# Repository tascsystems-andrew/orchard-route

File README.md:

# Orchard Route

**A GPU place-and-route engine for KiCad, native to Apple Silicon.**

Orchard Route routes printed circuit boards on the Mac GPU using
[MLX](https://github.com/ml-explore/mlx) and hand-written Metal kernels — no CUDA,
no cloud, no external EDA tooling in the loop. It reads a `.kicad_pcb`, negotiates
every net's copper simultaneously on the GPU, and writes back a routed board that
KiCad opens directly.

The name is a tip of the hat to
[OrthoRoute](https://github.com/bbenchoff/OrthoRoute), whose functional intent —
Manhattan-lattice GPU routing for KiCad — this project rebuilds natively for
Apple Silicon. No OrthoRoute code was ported; the architecture was redesigned
around what Metal and unified memory are actually good at.

## Status — working prototype

Flagship result (2026-07-18, MacBook Pro M4 Pro): a real 300×279 mm, 487-net
amplifier board — **all 410 routable nets negotiated to a fully legal routing**
(zero copper overlaps), 29.5 m of track, 1,259 vias (down from 2,824 at the
first legal route the same morning), 45°-smoothed output, ~7 minutes end-to-end
including parsing and write-back.

What works today:

- **`board.py`** — pure-Python `.kicad_pcb` parser (KiCad 5/9/10, no `pcbnew` needed)
- **`lattice.py`** — vectorized board → CSR lattice (both-directions layer model
  with direction preference; true rotated pad ownership; intentional pad-overlap
  allowances)
- **`wavefront.py`** — batched min-plus wavefront SSSP as an `mx.fast.metal_kernel`;
  the pull formulation needs **no atomics**, and 128 nets route per kernel launch
  (~0.5 ms per net; routing 32 nets costs the same wall-clock as routing 1)
- **`pathfinder.py`** — parallel PathFinder negotiation with asymmetric rip-up,
  keeper alternation, windowed stall escape, a post-legal refine pass, and
  legality-checked 45° smoothing; output is always legal, never optimistic
- **`constraints.py` / `place.py`** — the closed analog-constraint vocabulary and
  a deterministic annealing placement explorer (the router-independent half of
  `optimize_region`)
- **`backtrace.py` / `render.py` / `writeback.py`** — distance fields → paths →
  SVG render → routed *copies* of the board (tracks, vias, and component moves)
  that `kicad-cli` loads clean

Honest limitations, today: clearance classes are not yet enforced (grid pitch is
the de-facto clearance — active work), routing is 2-layer only (inner layers
unmodeled), a handful of nets on dense boards hit a known multi-party negotiation
standoff (active work), and the region place-and-route loop is designed
([REGION_SOLVER.md](REGION_SOLVER.md)) but not yet wired together.

## Benchmarks — measured against human ground truth

Seven open-hardware boards with professional placement and human routing
(KiCad's demo boards, Raspberry Pi's RP2040 reference designs, SparkFun's
RP2350 RedBoard, 1BitSquared's iCEBreakers). Protocol: keep the placement,
strip the human's tracks and vias, re-route from scratch, compare
(`bench/run_bench.py`; board sources and licenses in `bench/boards/SOURCES.md`).

| board | nets routed | wirelength vs human | vias vs human |
|---|---|---|---|
| SparkFun RedBoard RP2350 | **108/108** | **0.92×** | **0.78×** |
| iCEBreaker bitsy | 65/65 | 0.96× | 1.73× |
| KiCad pic-programmer | 34/34 | 1.03× | 8 vs 6 |
| RPi Pico VGA reference | 61/61 | 1.25× | 1.17× |
| RPi RP2040 minimal | 51/51 | 1.25× | 2.36× |
| iCEBreaker v1.0e | 123/126 | 1.18× | 1.98× |
| KiCad video demo (589 nets) | 369/371 | 1.09× | 2.52× |

Overall: 811/816 nets (99.4%), each board routed in 0.4–8 s of GPU negotiation
on an M4 Pro. On the SparkFun board the router beats the human layout on both
wirelength and via count simultaneously.

Read the ratios honestly: the router used **two** copper layers everywhere; the
humans had four on five of these boards (a handicap *against* the router — the
harness quantifies it per board). In the other direction, human copper passes
real clearance DRC while the router currently approximates clearance with grid
pitch — closing that gap is active work, as are the remaining 5 nets (a known
multi-party negotiation standoff pattern) and the via gap on dense 2-layer
boards (direction-preference calibration).

## Where it's going

The destination is not "another autorouter." It's an **agent-callable
place-and-route tool**:

```
optimize_region(components, region, constraints, k_candidates)
    -> ranked candidates + diagnostics
```

— hand an AI assistant a group of components, a patch of board, and constraints in a
closed vocabulary, and it places *and* routes just that region, returning ranked
options and machine-readable diagnostics ("net X unrouted, blocked by C8's courtyard;
4 mm more room east would clear it"). Full design in [ARCHITECTURE.md](ARCHITECTURE.md).

## Requirements

- Apple Silicon Mac (developed on M4 Pro; scales with GPU cores and unified memory)
- Python 3.12+, `mlx`, `numpy`
- KiCad 9/10 board files (KiCad itself only needed if you want `kicad-cli` DRC)

## Quickstart

```sh
python -m venv .venv && .venv/bin/pip install mlx numpy
.venv/bin/python pathfinder.py your_board.kicad_pcb --pitch 0.5 --layers F.Cu,B.Cu --svg out/routed.svg
.venv/bin/python writeback.py your_board.kicad_pcb out/routed.kicad_pcb --pitch 0.5 --layers F.Cu,B.Cu
```

Your input board is never modified; write-back refuses to write into the source
board's directory.

## License

Orchard Route is **dual-licensed**:

- **AGPL-3.0-only** (see [LICENSE](LICENSE)) for open use: if you distribute it,
  or run a modified version for others over a network, you must share your source.
- **Commercial licenses** for any use the AGPL doesn't fit — see
  [COMMERCIAL-LICENSE.md](COMMERCIAL-LICENSE.md).

Contributions require a lightweight relicensing grant — see
[CONTRIBUTING.md](CONTRIBUTING.md) before opening a PR.

Copyright © 2026 Andrew Sanche.

<!-- I got a fever, and the only prescription is more cowbell. -->

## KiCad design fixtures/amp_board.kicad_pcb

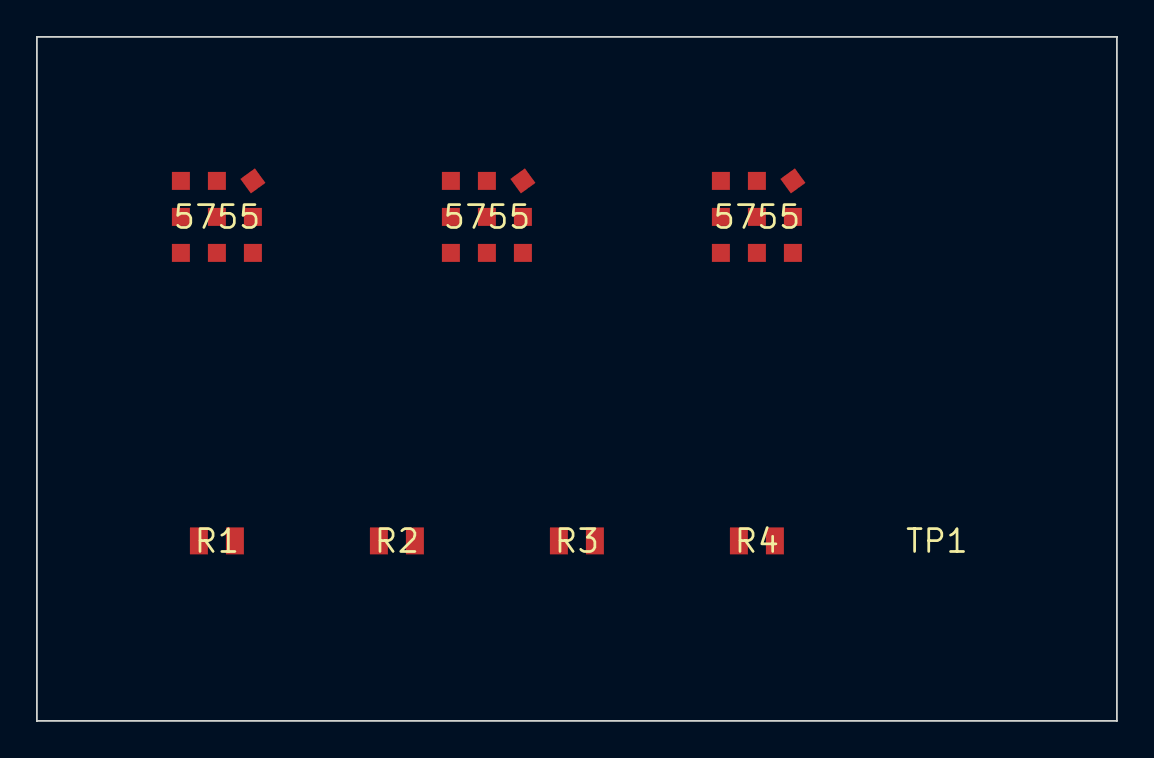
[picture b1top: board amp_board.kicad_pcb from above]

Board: 2 copper layers, 60.0 x 38.0 mm, 8 parts (0 on the bottom side), 4 nets, no tracks yet.

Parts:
5755, 5755#2, 5755#3: Valve_ECC-83-2
R1, R2, R3, R4: R_1206
TP1: TestPoint_Pad_D2.0mm

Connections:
GND: R3.2, R4.1, TP1.1
SIGA: R1.1, R4.2
SIGB: R1.2, R2.1
SIGC: R2.2, R3.1

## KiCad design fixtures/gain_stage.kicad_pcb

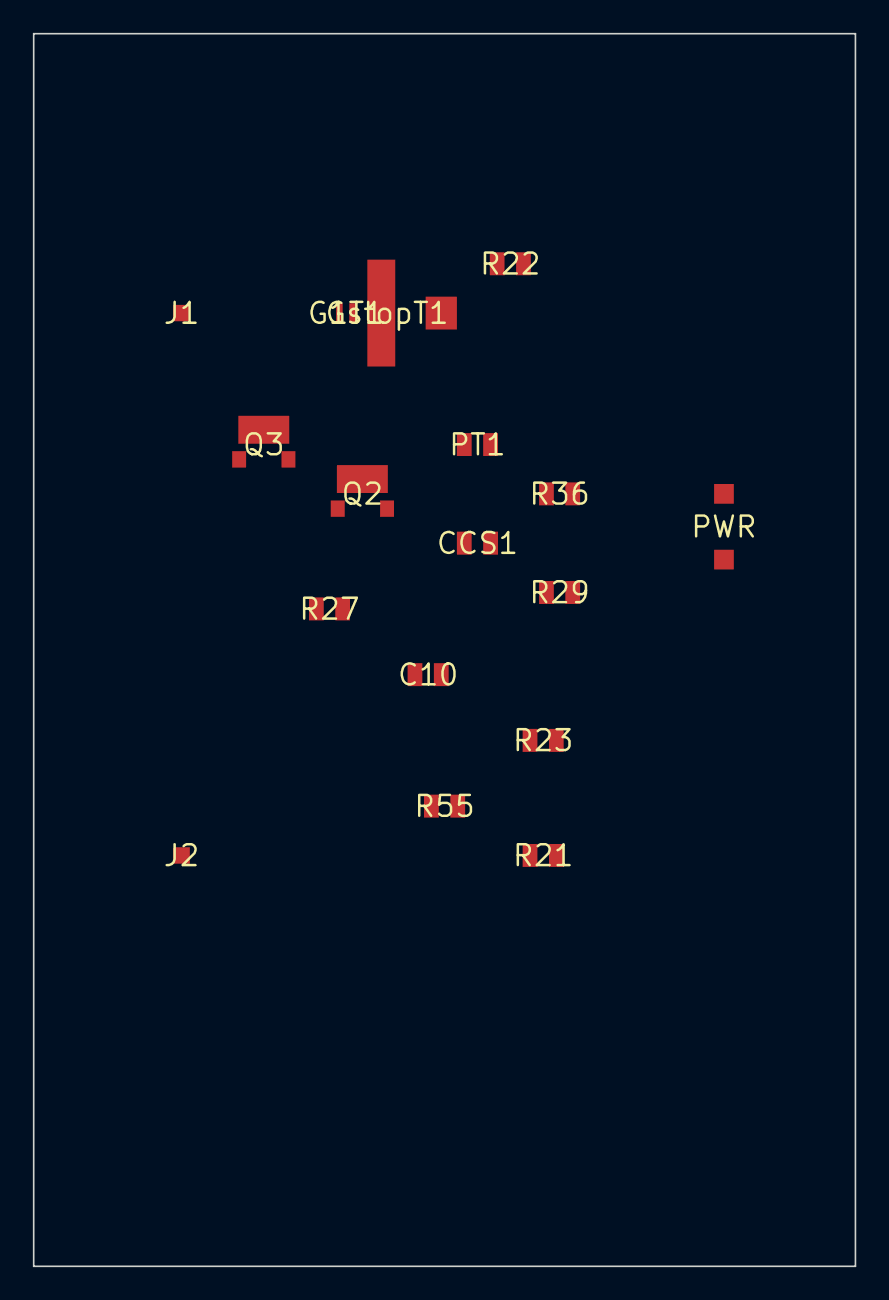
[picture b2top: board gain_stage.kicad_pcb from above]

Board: 2 copper layers, 50.0 x 75.0 mm, 17 parts (0 on the bottom side), 9 nets, no tracks yet.

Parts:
C10: R_1206
CCS1: R_1206
G1T1: R_1206
GstopT1: R_1206
J1, J2: R_1206
PT1: R_1206
PWR: R_1206
Q2, Q3: SOT-89
R21, R22, R23, R27, R29, R36, R55: R_1206

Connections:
CCSREF: CCS1.1, Q2.2, R36.1
GND-C: PWR.2, R21.2, R22.2, R27.2, R29.2, R36.2, R55.2
GRIDIN: G1T1.1, GstopT1.1, J1.1, R22.1
GSTOPLED: GstopT1.2, R27.1
PLATE: C10.1, G1T1.2, PT1.1, Q2.1, R23.1
PLATEOUT: C10.2, J2.1, PT1.2, R55.1
Q3A: Q3.1, Q3.3
VPLUS: CCS1.2, PWR.1, Q2.3, R29.1
VSENSE: R21.1, R23.2

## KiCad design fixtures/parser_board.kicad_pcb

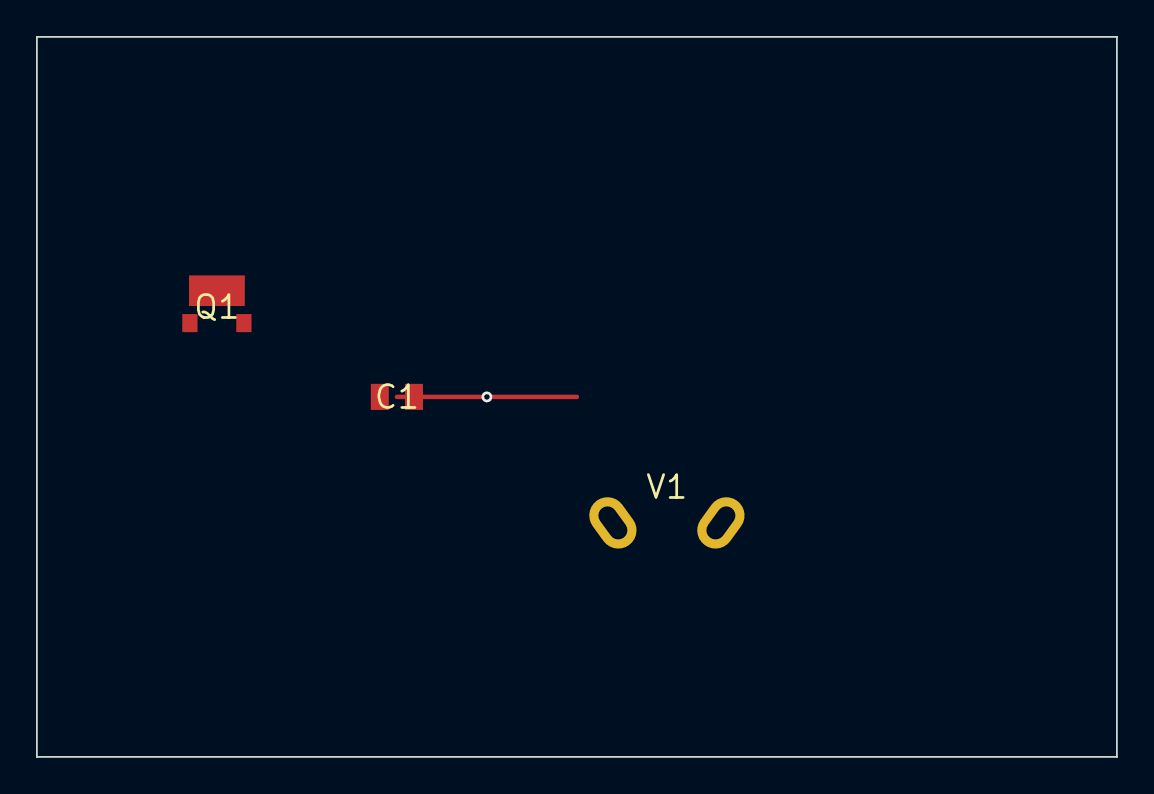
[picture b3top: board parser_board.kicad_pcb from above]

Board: 4 copper layers, 60.0 x 40.0 mm, 3 parts (0 on the bottom side), 2 nets.

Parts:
C1: C_0805_2012Metric
Q1: SOT-89-3
V1: Valve_ECC-83-2

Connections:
GND: C1.2, V1.4
PLATE1: Q1.3, V1.1

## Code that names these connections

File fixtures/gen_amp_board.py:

"""Generator for amp_board.kicad_pcb — the writeback/placement fixture.

The tests read the committed amp_board.kicad_pcb (+ amp_board.kicad_pro), NOT
this script; this file is the documented source of those bytes. Regenerate:

    python fixtures/gen_amp_board.py

A small amp board this test OWNS, replacing the old reads of Andrew's live hifi
board. It is shaped for test_place.py and test_writeback.py:

- THREE "5755" valves (duplicated designator -> 5755#1..#3 addressing), each a
  9-pad 3x3 grid rotated -90. Every asserted coordinate is hand-derivable:
  KiCad's -90 maps a footprint-local (ox, oy) to (fx - oy, fy + ox), so V1 at
  (20, 20, -90) puts its corner pad 1 (at -2 -2 216) at (22, 18), and a move of
  5755#1 to (120, 60, 180) (rotation delta 270) lands that pad at
  (120 + 2, 60 + 2) = (122, 62) with angle (216 + 270) % 360 = 126.
- four unrotated 2-pad resistors chained by four fully-routable nets
  (SIGA/SIGB/SIGC/GND) plus a 180-degrees single-pad test pin (TP1) on GND — so
  route_board() routes the board with ZERO failed nets at pitch 1.0, and the
  three single-pad valve nets (B+250, sig_in, Net-(V3-Pad1)) are named but
  unrouted (the width-cap tests need one of each). TP1's GND pad sits on B.Cu
  while the rest of GND is on F.Cu, so the GND route MUST drop a via — that
  keeps test_writeback's via-emission checks live (an all-F.Cu board routes
  flat, emits zero vias, and those checks go vacuous).
- the valves sit well clear of the resistor row, so their net-0 pads are pure
  obstacles and never block the route.

The sibling amp_board.kicad_pro carries a single Default net class (no
assignments/patterns), the "one Default class, no maps" shape test_writeback
resolves every net through; second_project.kicad_pro is a DIFFERENT project for
the parse-only path.
"""
import os

NETS = ["", "SIGA", "SIGB", "SIGC", "GND", "B+250", "sig_in", "Net-(V3-Pad1)"]
CODE = {n: i for i, n in enumerate(NETS)}


def pad(num, ox, oy, w, h, net, angle=None, layer="F.Cu"):
    at = f"(at {ox} {oy})" if angle is None else f"(at {ox} {oy} {angle})"
    return (f'\t\t(pad "{num}" smd rect {at} (size {w} {h}) '
            f'(layers "{layer}") (net {CODE[net]} "{net}"))')


def footprint(ref, x, y, rot, pads, lib="R_1206"):
    at = f"(at {x} {y})" if not rot else f"(at {x} {y} {rot})"
    body = [f'\t(footprint "{lib}" (layer "F.Cu")',
            f'\t\t{at}',
            f'\t\t(property "Reference" "{ref}" (at 0 0 0) (layer "F.SilkS"))']
    body.extend(pads)
    body.append("\t)")
    return "\n".join(body)


def valve(ref, x, y, pad1_net):
    """9-pad 3x3 grid (spacing 2 mm) rotated -90. Pad 1 is the (-2,-2) corner
    on pad1_net with an explicit 216-degrees angle (the move anchor); pads 2..9
    are net 0 obstacles."""
    grid = [(-2, -2), (0, -2), (2, -2), (-2, 0), (0, 0),
            (2, 0), (-2, 2), (0, 2), (2, 2)]
    pads = []
    for i, (ox, oy) in enumerate(grid, start=1):
        if i == 1:
            pads.append(pad("1", ox, oy, 1.0, 1.0, pad1_net, angle=216))
        else:
            pads.append(pad(str(i), ox, oy, 1.0, 1.0, ""))
    return footprint(ref, x, y, -90, pads, lib="Valve:Valve_ECC-83-2")


def res(ref, x, y, p1net, p2net):
    return footprint(ref, x, y, 0, [
        pad("1", -1.0, 0.0, 1.0, 1.5, p1net),
        pad("2", 1.0, 0.0, 1.0, 1.5, p2net),
    ])


def build():
    fps = [
        valve("5755", 20.0, 20.0, "B+250"),          # 5755#1
        valve("5755", 35.0, 20.0, "sig_in"),         # 5755#2
        valve("5755", 50.0, 20.0, "Net-(V3-Pad1)"),  # 5755#3
        res("R1", 20.0, 38.0, "SIGA", "SIGB"),
        res("R2", 30.0, 38.0, "SIGB", "SIGC"),
        res("R3", 40.0, 38.0, "SIGC", "GND"),
        res("R4", 50.0, 38.0, "GND", "SIGA"),
        # the pad angle folds in the footprint's 180 (as pcbnew writes it), so a
        # move back to rot 0 must drop the now-zero pad angle again.
        # TP1's GND pad is on B.Cu (every other pad is F.Cu): connecting GND to
        # it forces the router to drop exactly one VIA, which keeps
        # test_writeback's via-emission checks (count, net resolution, size/drill)
        # LIVE. A planar all-F.Cu board emits zero vias and those four checks go
        # vacuous — tautologies over an empty list — so a real via-writeback
        # regression would sail through. One cross-layer pad is the cheapest
        # honest way to force the via without adding a net or pad.
        footprint("TP1", 60.0, 38.0, 180, [
            pad("1", 0.0, 0.0, 1.5, 1.5, "GND", angle=180, layer="B.Cu")],
            lib="TestPoint:TestPoint_Pad_D2.0mm"),
    ]

    def edge(x0, y0, x1, y1):
        c = [(x0, y0), (x1, y0), (x1, y1), (x0, y1), (x0, y0)]
        return "\n".join(
            f'\t(gr_line (start {a[0]} {a[1]}) (end {b[0]} {b[1]}) '
            f'(layer "Edge.Cuts") (width 0.1))'
            for a, b in zip(c, c[1:]))

    return (
        '(kicad_pcb (version 20240108) (generator "gen_amp_board")\n'
        '\t(general (thickness 1.6))\n'
        '\t(paper "A4")\n'
        '\t(layers (0 "F.Cu" signal) (31 "B.Cu" signal))\n'
        + "".join(f'\t(net {i} "{n}")\n' for i, n in enumerate(NETS))
        + edge(10, 10, 70, 48) + "\n"
        + "\n".join(fps) + "\n)\n")


PRO = ('{\n  "net_settings": {\n    "classes": [\n'
       '      { "name": "Default", "clearance": 0.2, "track_width": 0.2,\n'
       '        "via_diameter": 0.6, "via_drill": 0.3 }\n'
       '    ]\n  }\n}\n')

SECOND_PRO = ('{\n  "net_settings": {\n    "classes": [\n'
              '      { "name": "Default", "clearance": 0.2, "track_width": 0.25,\n'
              '        "via_diameter": 0.8, "via_drill": 0.4 }\n'
              '    ]\n  }\n}\n')


if __name__ == "__main__":
    here = os.path.dirname(os.path.abspath(__file__))
    with open(os.path.join(here, "amp_board.kicad_pcb"), "w") as f:
        f.write(build())
    with open(os.path.join(here, "amp_board.kicad_pro"), "w") as f:
        f.write(PRO)
    with open(os.path.join(here, "second_project.kicad_pro"), "w") as f:
        f.write(SECOND_PRO)
    print("wrote amp_board.kicad_pcb, amp_board.kicad_pro, second_project.kicad_pro")
